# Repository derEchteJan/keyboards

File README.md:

# Keyboards
repo for keyboard stuff

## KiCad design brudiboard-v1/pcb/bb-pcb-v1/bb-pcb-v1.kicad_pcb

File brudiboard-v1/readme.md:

# Brudiboard

work in progress

### Dimensions

 - tkl pcb:   119.10 x 347.70 mm
 - tkl plate: 121.10 x 347.70 mm (h + 2mm)
 - frl pcb:    95.25 x 347.70 mm
 - frl plate:  97.25 x 347.70 mm (h + 2mm)

### Key count
 
| Row:    | Keys:   | Sockets: |
|---------|---------|----------|
| Func:   | 16      | 16       |
| Num:    | 17 (+1) | 17 (+2)  |
| tab:    | 17      | 17       |
| caps:   | 13      | 13 (+1)  |
| shift:  | 13 (+2) | 13 (+4)  |
| bottom: | 11 (+1) | 11 (+9)  |

- TKL: 87 (+4) keys = 83.65%, 87 - 103 Sockets
- FRL: 71 (+4) keys = 68.26%, 71 - 87  Sockets

### Required build materials

Amount for TKL (FRL in brackets)

- acrylic sheets 3,4,5mm
- hotswap sockets 103x (71x)
- 1N4148 diode 91x (75x)
- raspi pico
- usb breakout board
- switches 87-91x (71-75x)
- plate 1.5mm, material of choice
- wire for usb 28-30 AWG
- hex screw M3 20mm 4x, M3 15mm 4x, M2 10mm 2x
- 4mm M3 inserts 8x, 4mm M2 inserts 2x
- 8cm gasket strips 2mm 7x
 
### TODO
 - small stab holes can be enlarged
 - firmware:
   - minus has the kp_minus bound
   - up and down arrow are interchanged in via
   - spacebar is bound to MO(1)

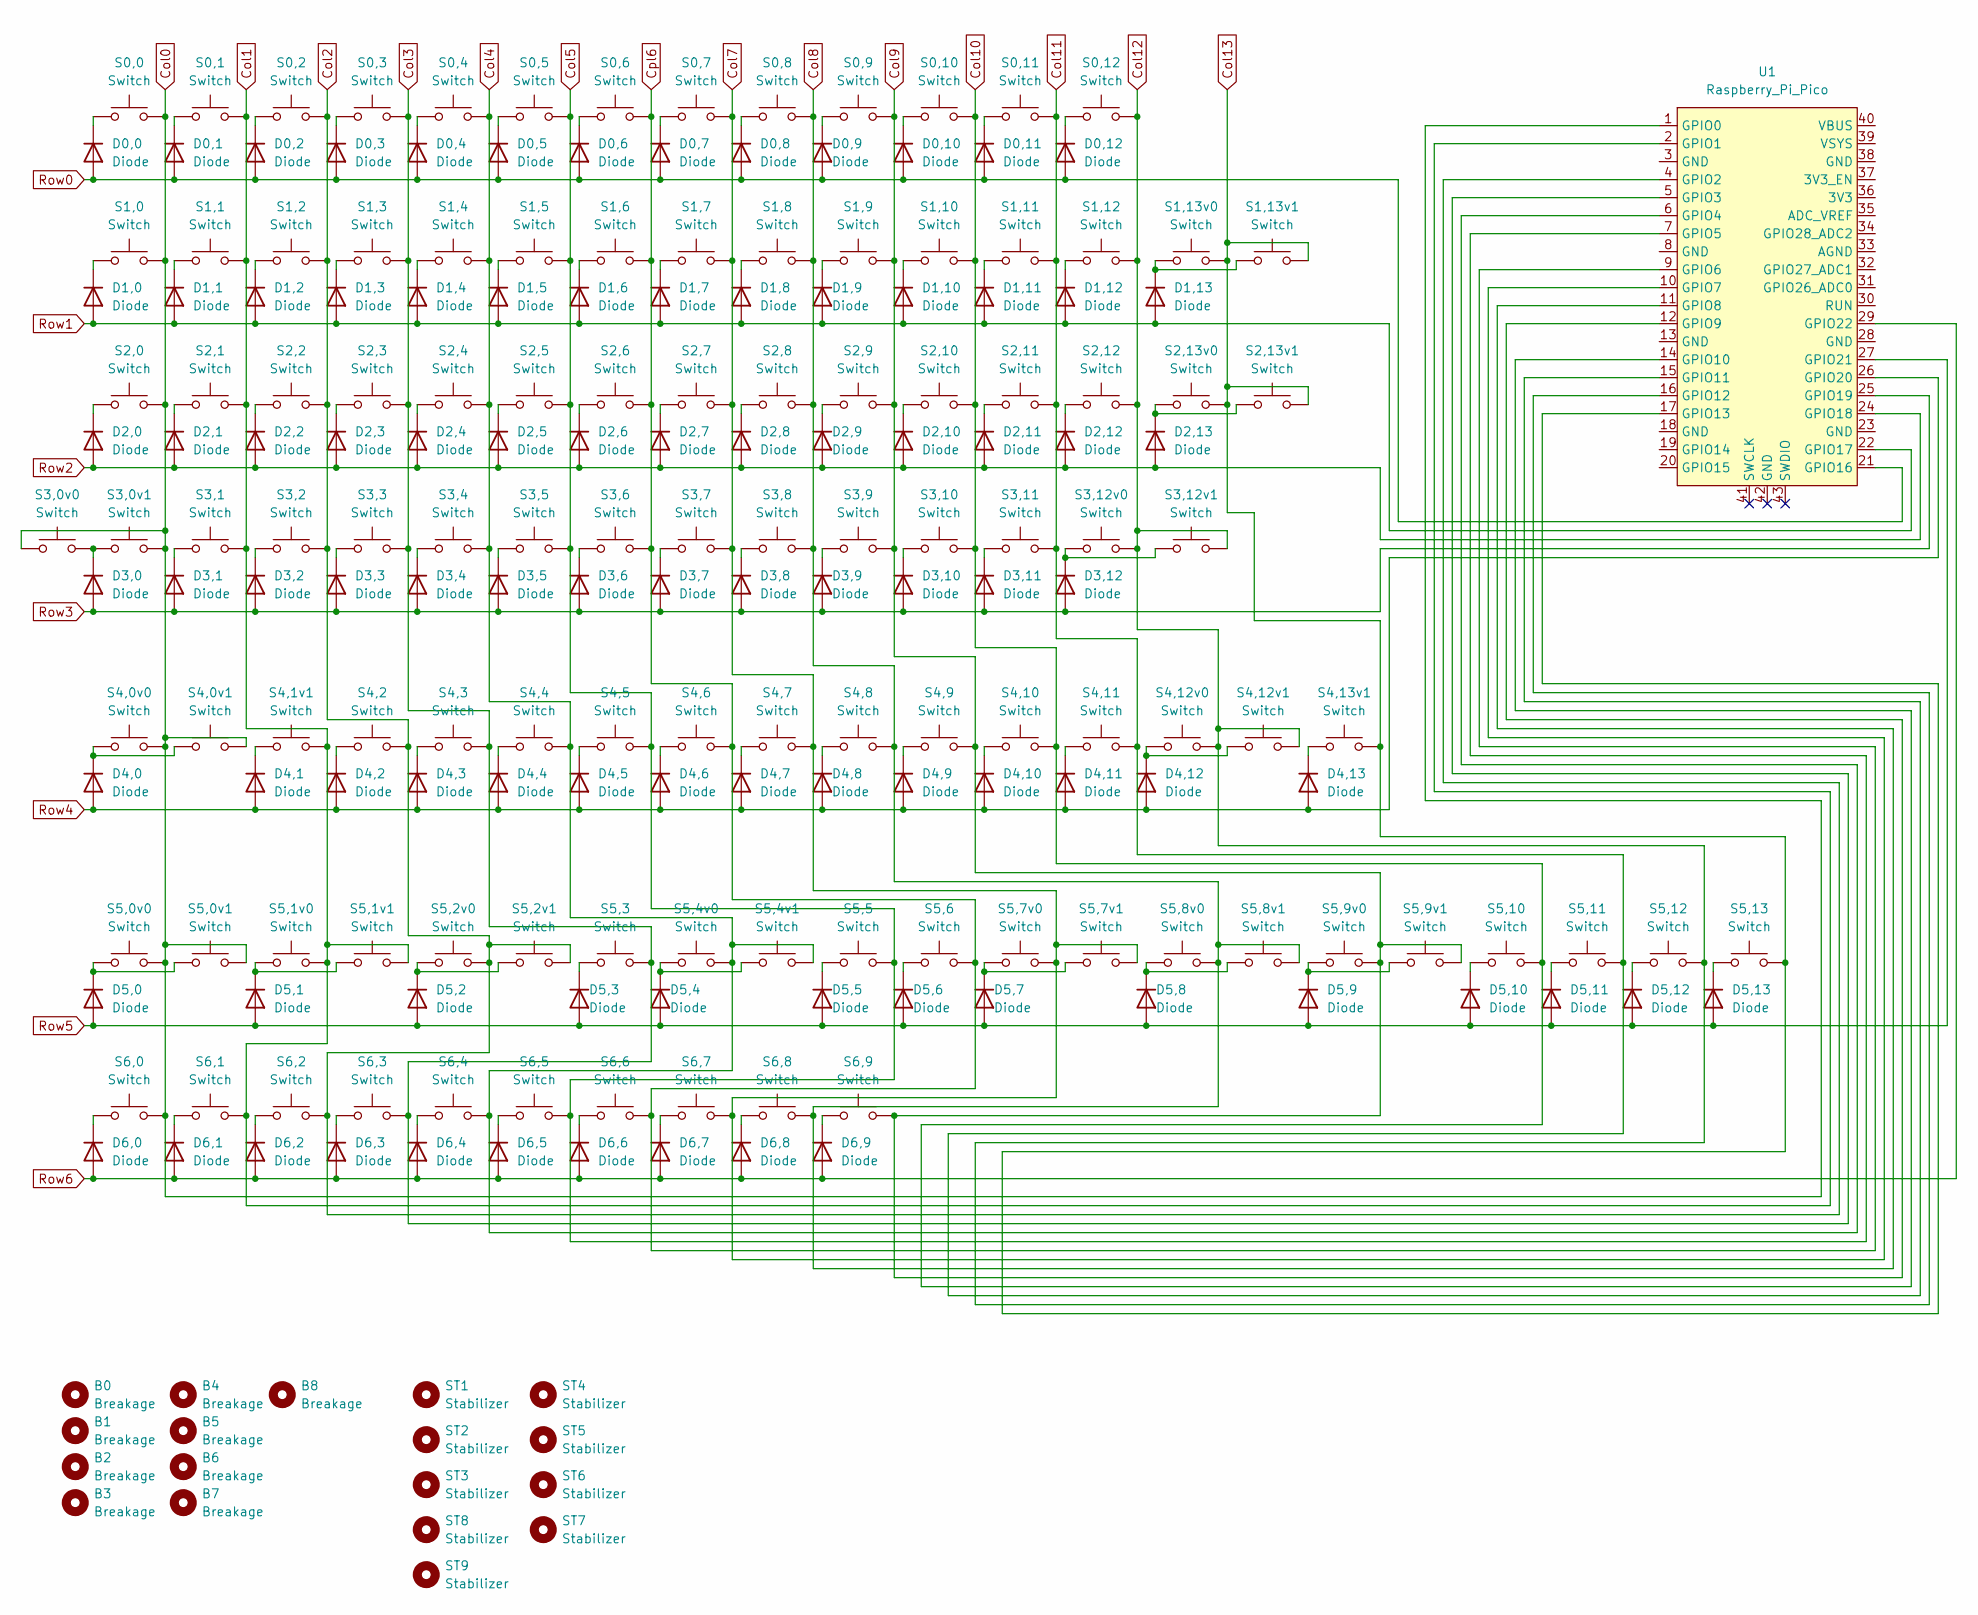
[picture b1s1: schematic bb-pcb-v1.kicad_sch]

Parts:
B0, B1, B2, B3, B4, B5, B6, B7, B8: Breakage; breakage
D0,0, D0,1, D0,2, D0,3, D0,4, D0,5, D0,6, D0,7, D0,8, D0,9, D0,10, D0,11, D0,12, D1,0, D1,1, D1,2, D1,3, D1,4, D1,5, D1,6, D1,7, D1,8, D1,9, D1,10, D1,11, D1,12, D1,13, D2,0, D2,1, D2,2, D2,3, D2,4, D2,5, D2,6, D2,7, D2,8, D2,9, D2,10, D2,11, D2,12, D2,13, D3,0, D3,1, D3,2, D3,3, D3,4, D3,5, D3,6, D3,7, D3,8, D3,9, D3,10, D3,11, D3,12, D4,0, D4,1, D4,2, D4,3, D4,4, D4,5, D4,6, D4,7, D4,8, D4,9, D4,10, D4,11, D4,12, D4,13, D5,0, D5,1, D5,2, D5,3, D5,4, D5,5, D5,6, D5,7, D5,8, D5,9, D5,10, D5,11, D5,12, D5,13, D6,0, D6,1, D6,2, D6,3, D6,4, D6,5, D6,6, D6,7, D6,8, D6,9: Diode; Diode_DO-35
S0,0, S0,1, S0,2, S0,3, S0,4, S0,5, S0,6, S0,7, S0,8, S0,9, S0,10, S0,11, S0,12, S1,0, S1,1, S1,2, S1,3, S1,4, S1,5, S1,6, S1,7, S1,8, S1,9, S1,10, S1,11, S1,12, S1,13v1, S2,1, S2,2, S2,3, S2,4, S2,5, S2,6, S2,7, S2,8, S2,9, S2,10, S2,11, S2,12, S2,13v1, S3,0v1, S3,1, S3,2, S3,3, S3,4, S3,5, S3,6, S3,7, S3,8, S3,9, S3,10, S3,11, S4,0v1, S4,1v1, S4,2, S4,3, S4,4, S4,5, S4,6, S4,7, S4,8, S4,9, S4,10, S4,11, S4,12v1, S4,13v1, S5,1v1, S5,8v1, S5,10, S5,11, S5,12, S5,13, S6,0, S6,1, S6,2, S6,3, S6,4, S6,5, S6,6, S6,7, S6,8, S6,9: Switch; Hotswap_MX_1.00u
S1,13v0: Switch; Hotswap_MX_2.00u
S2,0, S2,13v0, S5,0v1, S5,2v1, S5,7v1, S5,9v1: Switch; Hotswap_MX_1.50u
S3,0v0: Switch; Hotswap_MX_1.75u
S3,12v0, S4,0v0: Switch; Hotswap_MX_2.25u
S3,12v1: Switch; Hotswap_MX_ISOEnter
S4,12v0: Switch; Hotswap_MX_2.75u
S5,0v0, S5,1v0, S5,2v0, S5,6, S5,7v0, S5,8v0, S5,9v0: Switch; Hotswap_MX_1.25u
S5,3, S5,5: Switch; Hotswap_MX_3.00u
S5,4v0: Switch; Hotswap_MX_6.25u
S5,4v1: Switch; Hotswap_MX_7.00u
ST1, ST2, ST3, ST8, ST9: Stabilizer; Stabilizer_MX_2.00u_Exact
ST4: Stabilizer; Stabilizer_MX_6.25u_Exact
ST5: Stabilizer; Stabilizer_MX_7.00u_Exact
ST6: Stabilizer; Stabilizer_MX_3.00u_Exact_Left
ST7: Stabilizer; Stabilizer_MX_3.00u_Exact_Right
U1: Raspberry_Pi_Pico; Raspberry_Pi_Pico_Modified

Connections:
Col0: S0,0.2, S1,0.2, S2,0.2, S3,0v0.1, S3,0v1.2, S4,0v0.2, S4,0v1.2, S5,0v0.2, S5,0v1.2, S6,0.2, U1.1 (GPIO0)
Col1: S0,1.2, S1,1.2, S2,1.2, S3,1.2, S4,1v1.2, S5,1v0.2, S5,1v1.2, S6,1.2, U1.2 (GPIO1)
Col2: S0,2.2, S1,2.2, S2,2.2, S3,2.2, S4,2.2, S5,2v0.2, S5,2v1.2, S6,2.2, U1.4 (GPIO2)
Col3: S0,3.2, S1,3.2, S2,3.2, S3,3.2, S4,3.2, S5,3.2, S6,3.2, U1.5 (GPIO3)
Col4: S0,4.2, S1,4.2, S2,4.2, S3,4.2, S4,4.2, S5,4v0.2, S5,4v1.2, S6,4.2, U1.6 (GPIO4)
Col5: S0,5.2, S1,5.2, S2,5.2, S3,5.2, S4,5.2, S5,5.2, S6,5.2, U1.7 (GPIO5)
Col7: S0,7.2, S1,7.2, S2,7.2, S3,7.2, S4,7.2, S5,7v0.2, S5,7v1.2, S6,7.2, U1.10 (GPIO7)
Col8: S0,8.2, S1,8.2, S2,8.2, S3,8.2, S4,8.2, S5,8v0.2, S5,8v1.2, S6,8.2, U1.11 (GPIO8)
Col9: S0,9.2, S1,9.2, S2,9.2, S3,9.2, S4,9.2, S5,9v0.2, S5,9v1.2, S6,9.2, U1.12 (GPIO9)
Col10: S0,10.2, S1,10.2, S2,10.2, S3,10.2, S4,10.2, S5,10.2, U1.14 (GPIO10)
Col11: S0,11.2, S1,11.2, S2,11.2, S3,11.2, S4,11.2, S5,11.2, U1.15 (GPIO11)
Col12: S0,12.2, S1,12.2, S2,12.2, S3,12v0.2, S3,12v1.2, S4,12v0.2, S4,12v1.2, S5,12.2, U1.16 (GPIO12)
Col13: S1,13v0.2, S1,13v1.2, S2,13v0.2, S2,13v1.2, S4,13v1.2, S5,13.2, U1.17 (GPIO13)
Cpl6: S0,6.2, S1,6.2, S2,6.2, S3,6.2, S4,6.2, S5,6.2, S6,6.2, U1.9 (GPIO6)
unnamed: D0,0.1 (K), S0,0.1
unnamed: D0,1.1 (K), S0,1.1
unnamed: D0,2.1 (K), S0,2.1
unnamed: D0,3.1 (K), S0,3.1
unnamed: D0,4.1 (K), S0,4.1
unnamed: D0,5.1 (K), S0,5.1
unnamed: D0,6.1 (K), S0,6.1
unnamed: D0,7.1 (K), S0,7.1
unnamed: D0,8.1 (K), S0,8.1
unnamed: D0,9.1 (K), S0,9.1
unnamed: D0,10.1 (K), S0,10.1
unnamed: D0,11.1 (K), S0,11.1
unnamed: D0,12.1 (K), S0,12.1
unnamed: D1,0.1 (K), S1,0.1
unnamed: D1,1.1 (K), S1,1.1
unnamed: D1,2.1 (K), S1,2.1
unnamed: D1,3.1 (K), S1,3.1
unnamed: D1,4.1 (K), S1,4.1
unnamed: D1,5.1 (K), S1,5.1
unnamed: D1,6.1 (K), S1,6.1
unnamed: D1,7.1 (K), S1,7.1
unnamed: D1,8.1 (K), S1,8.1
unnamed: D1,9.1 (K), S1,9.1
unnamed: D1,10.1 (K), S1,10.1
unnamed: D1,11.1 (K), S1,11.1
unnamed: D1,12.1 (K), S1,12.1
unnamed: D1,13.1 (K), S1,13v0.1, S1,13v1.1
unnamed: D2,0.1 (K), S2,0.1
unnamed: D2,1.1 (K), S2,1.1
unnamed: D2,2.1 (K), S2,2.1
unnamed: D2,3.1 (K), S2,3.1
unnamed: D2,4.1 (K), S2,4.1
unnamed: D2,5.1 (K), S2,5.1
unnamed: D2,6.1 (K), S2,6.1
unnamed: D2,7.1 (K), S2,7.1
unnamed: D2,8.1 (K), S2,8.1
unnamed: D2,9.1 (K), S2,9.1
unnamed: D2,10.1 (K), S2,10.1
unnamed: D2,11.1 (K), S2,11.1
unnamed: D2,12.1 (K), S2,12.1
unnamed: D2,13.1 (K), S2,13v0.1, S2,13v1.1
unnamed: D3,0.1 (K), S3,0v0.2, S3,0v1.1
unnamed: D3,1.1 (K), S3,1.1
unnamed: D3,2.1 (K), S3,2.1
unnamed: D3,3.1 (K), S3,3.1
unnamed: D3,4.1 (K), S3,4.1
unnamed: D3,5.1 (K), S3,5.1
unnamed: D3,6.1 (K), S3,6.1
unnamed: D3,7.1 (K), S3,7.1
unnamed: D3,8.1 (K), S3,8.1
unnamed: D3,9.1 (K), S3,9.1
unnamed: D3,10.1 (K), S3,10.1
unnamed: D3,11.1 (K), S3,11.1
unnamed: D3,12.1 (K), S3,12v0.1, S3,12v1.1
unnamed: D4,0.1 (K), S4,0v0.1, S4,0v1.1
unnamed: D4,1.1 (K), S4,1v1.1
unnamed: D4,2.1 (K), S4,2.1
unnamed: D4,3.1 (K), S4,3.1
unnamed: D4,4.1 (K), S4,4.1
unnamed: D4,5.1 (K), S4,5.1
unnamed: D4,6.1 (K), S4,6.1
unnamed: D4,7.1 (K), S4,7.1
unnamed: D4,8.1 (K), S4,8.1
unnamed: D4,9.1 (K), S4,9.1
unnamed: D4,10.1 (K), S4,10.1
unnamed: D4,11.1 (K), S4,11.1
unnamed: D4,12.1 (K), S4,12v0.1, S4,12v1.1
unnamed: D4,13.1 (K), S4,13v1.1
unnamed: D5,0.1 (K), S5,0v0.1, S5,0v1.1
unnamed: D5,1.1 (K), S5,1v0.1, S5,1v1.1
unnamed: D5,2.1 (K), S5,2v0.1, S5,2v1.1
unnamed: D5,3.1 (K), S5,3.1
unnamed: D5,4.1 (K), S5,4v0.1, S5,4v1.1
unnamed: D5,5.1 (K), S5,5.1
unnamed: D5,6.1 (K), S5,6.1
unnamed: D5,7.1 (K), S5,7v0.1, S5,7v1.1
unnamed: D5,8.1 (K), S5,8v0.1, S5,8v1.1
unnamed: D5,9.1 (K), S5,9v0.1, S5,9v1.1
unnamed: D5,10.1 (K), S5,10.1
unnamed: D5,11.1 (K), S5,11.1
unnamed: D5,12.1 (K), S5,12.1
unnamed: D5,13.1 (K), S5,13.1
unnamed: D6,0.1 (K), S6,0.1
unnamed: D6,1.1 (K), S6,1.1
unnamed: D6,2.1 (K), S6,2.1
unnamed: D6,3.1 (K), S6,3.1
unnamed: D6,4.1 (K), S6,4.1
unnamed: D6,5.1 (K), S6,5.1
unnamed: D6,6.1 (K), S6,6.1
unnamed: D6,7.1 (K), S6,7.1
unnamed: D6,8.1 (K), S6,8.1
unnamed: D6,9.1 (K), S6,9.1
Row0: D0,0.2 (A), D0,1.2 (A), D0,2.2 (A), D0,3.2 (A), D0,4.2 (A), D0,5.2 (A), D0,6.2 (A), D0,7.2 (A), D0,8.2 (A), D0,9.2 (A), D0,10.2 (A), D0,11.2 (A), D0,12.2 (A), U1.21 (GPIO16)
Row1: D1,0.2 (A), D1,1.2 (A), D1,2.2 (A), D1,3.2 (A), D1,4.2 (A), D1,5.2 (A), D1,6.2 (A), D1,7.2 (A), D1,8.2 (A), D1,9.2 (A), D1,10.2 (A), D1,11.2 (A), D1,12.2 (A), D1,13.2 (A), U1.22 (GPIO17)
Row2: D2,0.2 (A), D2,1.2 (A), D2,2.2 (A), D2,3.2 (A), D2,4.2 (A), D2,5.2 (A), D2,6.2 (A), D2,7.2 (A), D2,8.2 (A), D2,9.2 (A), D2,10.2 (A), D2,11.2 (A), D2,12.2 (A), D2,13.2 (A), U1.24 (GPIO18)
Row3: D3,0.2 (A), D3,1.2 (A), D3,2.2 (A), D3,3.2 (A), D3,4.2 (A), D3,5.2 (A), D3,6.2 (A), D3,7.2 (A), D3,8.2 (A), D3,9.2 (A), D3,10.2 (A), D3,11.2 (A), D3,12.2 (A), U1.25 (GPIO19)
Row4: D4,0.2 (A), D4,1.2 (A), D4,2.2 (A), D4,3.2 (A), D4,4.2 (A), D4,5.2 (A), D4,6.2 (A), D4,7.2 (A), D4,8.2 (A), D4,9.2 (A), D4,10.2 (A), D4,11.2 (A), D4,12.2 (A), D4,13.2 (A), U1.26 (GPIO20)
Row5: D5,0.2 (A), D5,1.2 (A), D5,2.2 (A), D5,3.2 (A), D5,4.2 (A), D5,5.2 (A), D5,6.2 (A), D5,7.2 (A), D5,8.2 (A), D5,9.2 (A), D5,10.2 (A), D5,11.2 (A), D5,12.2 (A), D5,13.2 (A), U1.27 (GPIO21)
Row6: D6,0.2 (A), D6,1.2 (A), D6,2.2 (A), D6,3.2 (A), D6,4.2 (A), D6,5.2 (A), D6,6.2 (A), D6,7.2 (A), D6,8.2 (A), D6,9.2 (A), U1.29 (GPIO22)

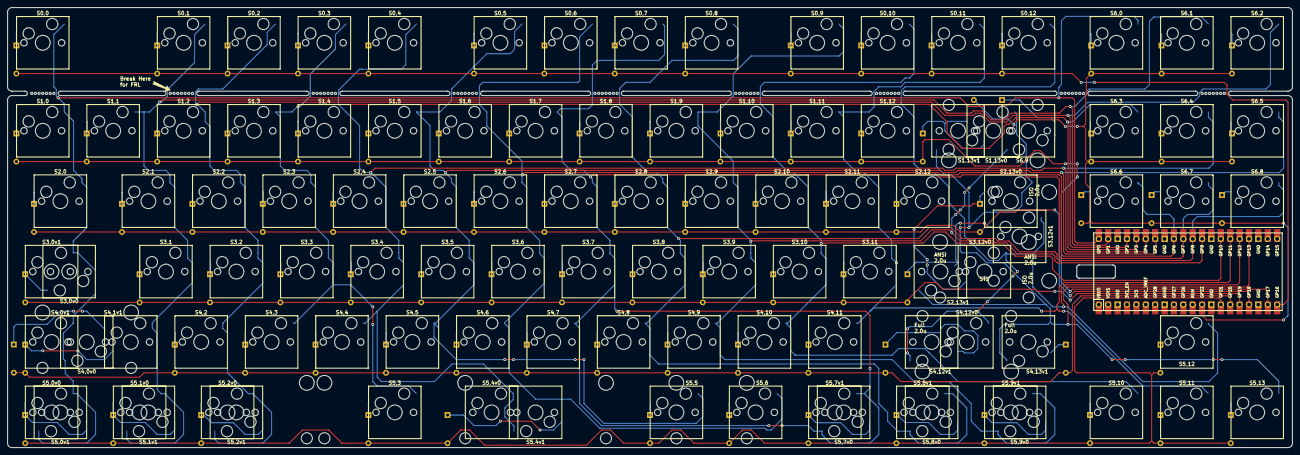
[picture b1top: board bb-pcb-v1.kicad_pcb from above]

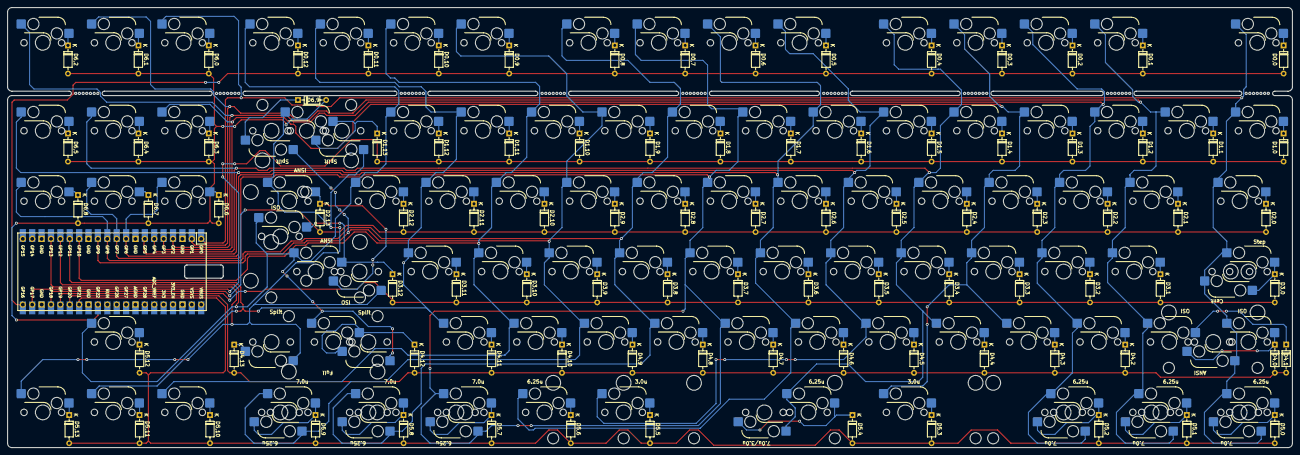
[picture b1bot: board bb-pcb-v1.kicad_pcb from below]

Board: 2 copper layers, 347.7 x 119.1 mm, 216 parts (93 on the bottom side), 113 nets.

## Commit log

2024-02-19 initial
2024-02-20 cleanup, re-add calibration files
2024-02-21 6x5-ortho-v1 split implementation
2024-02-25 6x5-ortho-v1 split via
2024-03-02 cycle7-plate initial files
2024-03-04 brudiboard-v1 initial
2024-03-10 brudiboard-v1 plate and pcb finished
2024-03-10 brudiboard-v1 top view initial
2024-03-11 brudiboard-v1 frl case top view added
2024-03-13 brudiboard-v1 pcb v1 finalized and exported
2024-03-21 brudiboard-v1 case design modifiactions + plate production files
2024-05-14 brudiboard-v1 case production files + pcb rev 3
2024-05-15 brudiboard-v1 case sketch adjustments
2024-05-20 brudiboard-v1 adjusted layout for via
2024-05-20 brudiboard-v1 qmk via implementation
2024-05-21 brudiboard-v1 case adjustments
2024-05-24 brudiboard-v1 case adjustments and firmware build added
2024-05-27 brudiboard-v1 matrix adjusted, deprecated gerbers deleted
2024-05-27 brudiboard-v1 added special edition pcb
2024-05-29 brudiboard-v1 plate produciton files and tkl sideview added
2024-06-11 brudiboard-v1 corrected both adjusted case templates
2024-06-18 brudiboard-v1 lto order files
2024-06-26 brudiboard-v1 added engravings and alternative foot
2024-07-24 brudiboard-v1 added engravings
2024-10-30 plate changes prod
2024-10-30 brudiboard-v1: generated gerbers without fillzones front and back
2024-12-21 brudiboard-v1 db2 frl adjustments
2025-02-18 brudiboard-v1 adjusted screw holes FRL
2025-02-19 brudiboard-v1 adjusted screw holes tkl
2025-04-11 brudiboard-v1 adjusted layout files
2025-06-29 add bort.jpeg
